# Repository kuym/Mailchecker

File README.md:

MailChecker2
============

This Electric Imp-powered device detects motion and reports it to you over the web.  It was originally designed to be stuck to a mailbox door
to notify you over WiFi when mail is delivered.  It could also be used to monitor doors (including garage or pet doors), valuables that you
don't want moved or cookie jars you want to keep children out of.

## Features

The board features an accelerometer, light sensor and Lithium-ion/polymer battery recharging built in.  It achieves approximately one month
of use between charges per 100mAh of battery capacity, assuming two motion activations per day.

This is a totally valid design but I intend to publish a newer version with Li-ion battery protection for unregulated cells.  The battery
attach terminals on the bottom are designed for a [138mAh Li-ion cell from HobbyKing](http://hobbyking.com/hobbyking/store/__37575__ZIPPY_138mAh_20C_Single_Cell_USA_Warehouse_.html),
which is an unregulated cell (and therefore can be fatally over-discharged by this design.)

## Board

[Order one from OSHPark](http://oshpark.com/shared_projects/IBBSjENY).

Submit the EAGLE sources or [gerber zip (Mailchecker2.zip)](../master/production/Mailchecker2) to your PCB fabricator to order your own.

## Parts

Check the [Bill of Materials](../master/production/Mailchecker2/Mailchecker2-parts.txt) to see what you already have that's an exact or close fit.
R1, R4 and R6 have important values.  All other resistors may be increased to 2x or decreased to 0.5x their specified value.
All capacitors may be increased of 2x their specified value.

## Assembly

## Firmware

Blink up the Imp and paste the squirrel source code in the [Electric Imp IDE](http://ide.electricimp.com).

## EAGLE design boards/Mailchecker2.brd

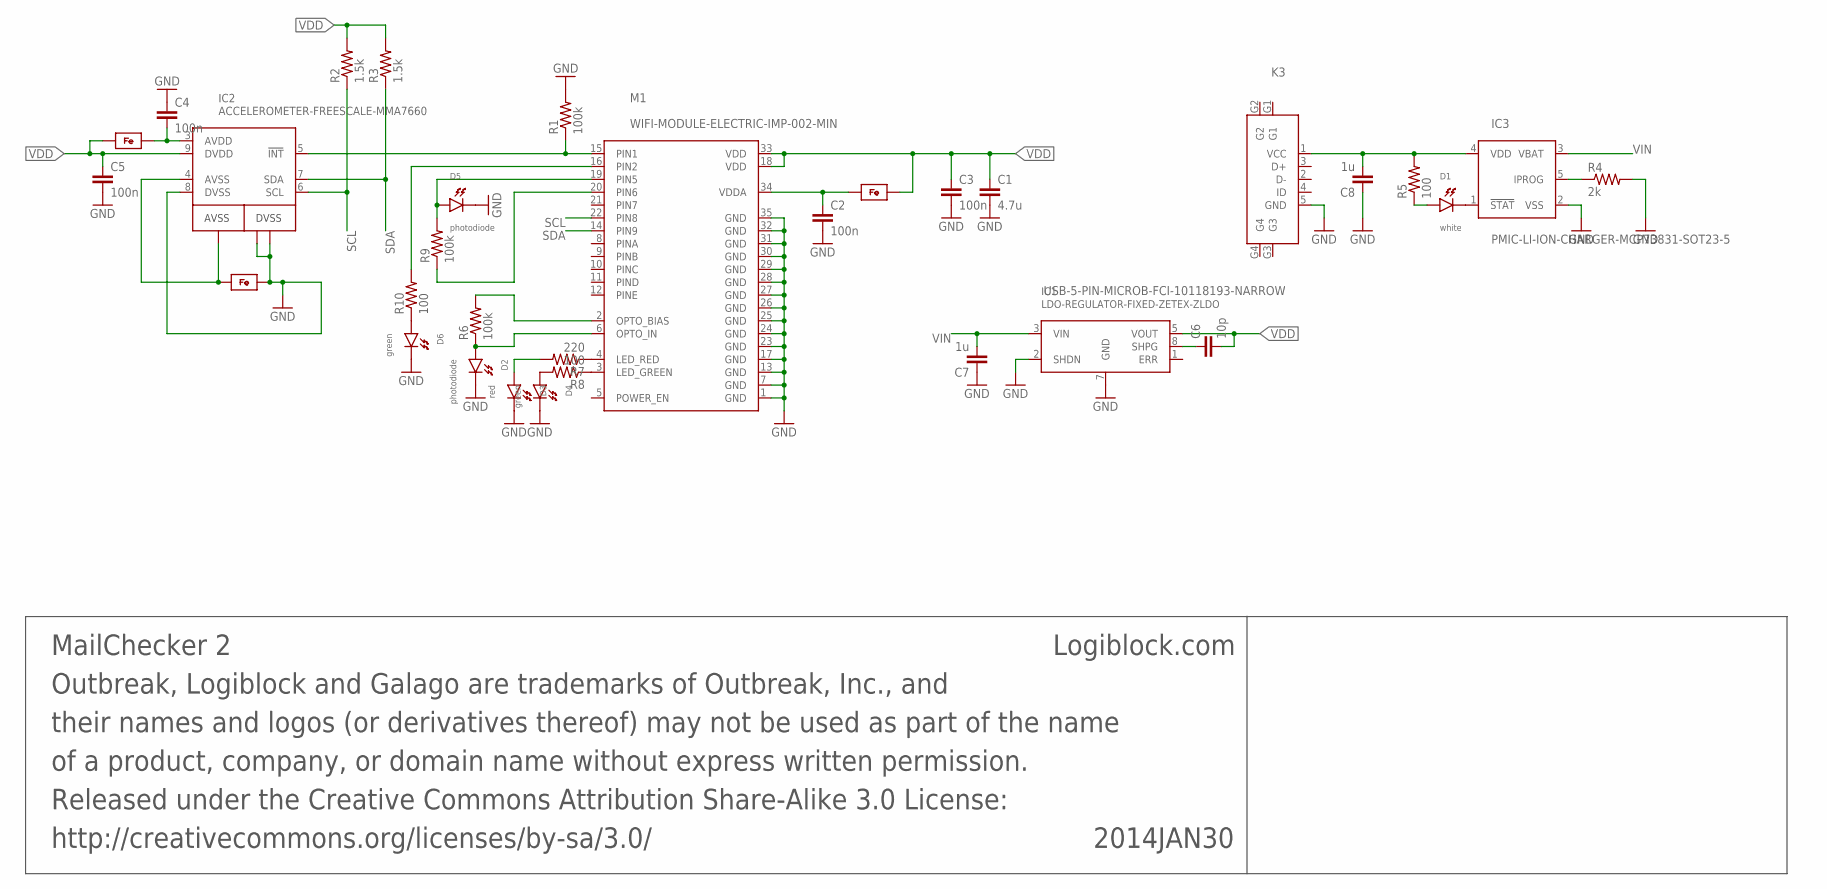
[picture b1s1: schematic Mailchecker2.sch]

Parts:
2014JAN30: MailChecker 2; INFO-BLOCK
C1: 4.7u; 0805-MIN
C2, C3, C4, C5: 100n; 0402-MIN
C6: 10p; 0402-MIN
C7, C8: 1u; 0603-MIN
D1: white; 0603-DIODE-MIN
D2, D5: photodiode; 0603-DIODE-MIN
D3: red; 0603-DIODE-MIN
D4, D6: green; 0603-DIODE-MIN
FB1, FB2, FB3: FERRITE-BEAD-0603-MIN; 0603-MIN
IC1: LDO-REGULATOR-FIXED-ZETEX-ZLDO; SM8-ZETEX
IC2: ACCELEROMETER-FREESCALE-MMA7660; QFN10-3X3MM-FREESCALE-MMA7660
IC3: PMIC-LI-ION-CHARGER-MCP73831-SOT23-5; SOT23-5
K3: USB-5-PIN-MICROB-FCI-10118193-NARROW; USB-MICROB-FCI-10118193-NARROW
M1: WIFI-MODULE-ELECTRIC-IMP-002-MIN; ELECTRIC-IMP-002-MIN
R1, R6, R9: 100k; 0402-MIN
R2, R3: 1.5k; 0402-MIN
R4: 2k; 0402-MIN
R5, R8, R10: 100; 0402-MIN
R7: 220; 0402-MIN

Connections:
AVDD: C4.1, FB3.2, IC2.3 (AVDD)
AVSS: FB2.1, IC2.1 (G3), IC2.4 (AVSS)
GND: C1.1, C2.1, C3.1, C4.2, C5.1, C7.2, C8.2, D2.K, D3.K, D4.K, D5.K, D6.K, FB2.2, IC1.2 (SHDN), IC1.7 (GND), IC2.8 (DVSS), IC2.G1, IC2.G2, IC3.2 (VSS), K3.5 (GND), M1.1 (GND), M1.7 (GND), M1.13 (GND), M1.17 (GND), M1.23 (GND), M1.24 (GND), M1.25 (GND), M1.26 (GND), M1.27 (GND), M1.28 (GND), M1.29 (GND), M1.30 (GND), M1.31 (GND), M1.32 (GND), M1.35 (GND), R1.2, R4.2
INT: IC2.5 (!INT), M1.15 (PIN1), R1.1
IPROG: IC3.5 (IPROG), R4.1
unnamed: M1.2 (OPTO_BIAS), R6.2
unnamed: M1.20 (PIN6), R9.1
unnamed: D1.K, IC3.1 (!STAT)
unnamed: D1.A, R5.1
unnamed: D2.A, M1.6 (OPTO_IN), R6.1
unnamed: M1.4 (LED_RED), R7.1
unnamed: M1.3 (LED_GREEN), R8.1
unnamed: D4.A, R8.2
unnamed: D3.A, R7.2
unnamed: D5.A, M1.19 (PIN5), R9.2
unnamed: M1.16 (PIN2), R10.2
unnamed: D6.A, R10.1
SCL: IC2.6 (SCL), M1.22 (PIN8), R2.1
SDA: IC2.7 (SDA), M1.14 (PIN9), R3.1
SHAPING: C6.2, IC1.8 (SHPG)
VCHARGE: C8.1, IC3.4 (VDD), K3.1 (VCC), R5.2
VDD: C1.2, C3.2, C5.2, C6.1, FB1.2, FB3.1, IC1.5 (VOUT), IC2.9 (DVDD), M1.18 (VDD), M1.33 (VDD), R2.2, R3.2
VDDA: C2.2, FB1.1, M1.34 (VDDA)
VIN: C7.1, IC1.3 (VIN), IC3.3 (VBAT)

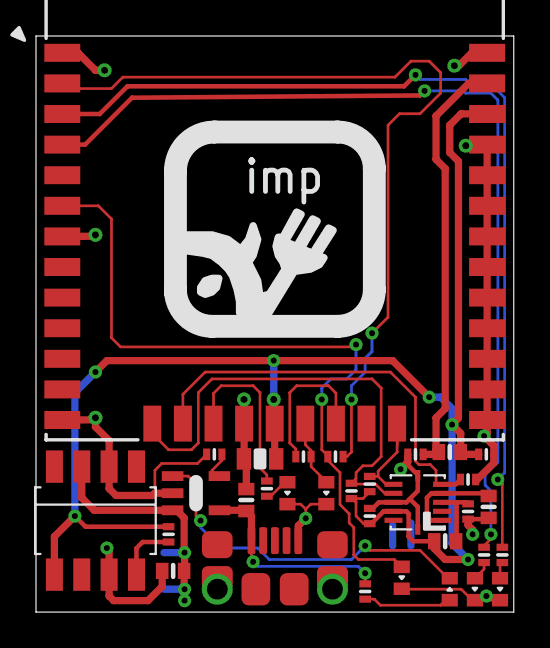
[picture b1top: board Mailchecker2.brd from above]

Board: 2 copper layers, 26.5 x 32.0 mm, 33 parts (0 on the bottom side), 24 nets.

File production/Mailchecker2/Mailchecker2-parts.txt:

Partlist

Exported from Mailchecker2.sch at 2014Jan30 12:10

EAGLE Version 6.1.0 Copyright (c) 1988-2012 CadSoft

Assembly variant: 

Part     Value                                Device                               Package                        Library  Sheet

C1       4.7u                                 CAP-0805-MIN                         0805-MIN                       Outbreak 1
C2       100n                                 CAP-0402-MIN                         0402-MIN                       Outbreak 1
C3       100n                                 CAP-0402-MIN                         0402-MIN                       Outbreak 1
C4       100n                                 CAP-0402-MIN                         0402-MIN                       Outbreak 1
C5       100n                                 CAP-0402-MIN                         0402-MIN                       Outbreak 1
C6       10p                                  CAP-0402-MIN                         0402-MIN                       Outbreak 1
C7       1u                                   CAP-0603-MIN                         0603-MIN                       Outbreak 1
C8       1u                                   CAP-0603-MIN                         0603-MIN                       Outbreak 1
D1       white                                LED-0603-MIN                         0603-DIODE-MIN                 Outbreak 1
D2       photodiode                           LED-0603-MIN                         0603-DIODE-MIN                 Outbreak 1
D3       red                                  LED-0603-MIN                         0603-DIODE-MIN                 Outbreak 1
D4       green                                LED-0603-MIN                         0603-DIODE-MIN                 Outbreak 1
D5       photodiode                           LED-0603-MIN                         0603-DIODE-MIN                 Outbreak 1
D6       green                                LED-0603-MIN                         0603-DIODE-MIN                 Outbreak 1
FB1                                           FERRITE-BEAD-0603-MIN                0603-MIN                       Outbreak 1
FB2                                           FERRITE-BEAD-0603-MIN                0603-MIN                       Outbreak 1
FB3                                           FERRITE-BEAD-0603-MIN                0603-MIN                       Outbreak 1
IC1      LDO-REGULATOR-FIXED-ZETEX-ZLDO       LDO-REGULATOR-FIXED-ZETEX-ZLDO       SM8-ZETEX                      Outbreak 1
IC2      ACCELEROMETER-FREESCALE-MMA7660      ACCELEROMETER-FREESCALE-MMA7660      QFN10-3X3MM-FREESCALE-MMA7660  Outbreak 1
IC3      PMIC-LI-ION-CHARGER-MCP73831-SOT23-5 PMIC-LI-ION-CHARGER-MCP73831-SOT23-5 SOT23-5                        Outbreak 1
K3       USB-5-PIN-MICROB-FCI-10118193-NARROW USB-5-PIN-MICROB-FCI-10118193-NARROW USB-MICROB-FCI-10118193-NARROW Outbreak 1
M1       WIFI-MODULE-ELECTRIC-IMP-002-MIN     WIFI-MODULE-ELECTRIC-IMP-002-MIN     ELECTRIC-IMP-002-MIN           Outbreak 1
R1       100k                                 RESISTOR-0402-MIN                    0402-MIN                       Outbreak 1
R2       1.5k                                 RESISTOR-0402-MIN                    0402-MIN                       Outbreak 1
R3       1.5k                                 RESISTOR-0402-MIN                    0402-MIN                       Outbreak 1
R4       2k                                   RESISTOR-0402-MIN                    0402-MIN                       Outbreak 1
R5       100                                  RESISTOR-0402-MIN                    0402-MIN                       Outbreak 1
R6       100k                                 RESISTOR-0402-MIN                    0402-MIN                       Outbreak 1
R7       220                                  RESISTOR-0402-MIN                    0402-MIN                       Outbreak 1
R8       100                                  RESISTOR-0402-MIN                    0402-MIN                       Outbreak 1
R9       100k                                 RESISTOR-0402-MIN                    0402-MIN                       Outbreak 1
R10      100                                  RESISTOR-0402-MIN                    0402-MIN                       Outbreak 1

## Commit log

2014-01-30 Initial commit of working design.
2014-01-30 Update documentation.
2014-01-30 fixup OSHPark link
2014-01-30 Added poster image
2014-01-30 Adding larger photo to make up for Twitter's terrible tiny compressed version.

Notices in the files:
parts and their libraries:
Outbreak: Released under the Creative Commons Attribution Share-Alike 3.0 License:
Outbreak: http://creativecommons.org/licenses/by-sa/3.0
